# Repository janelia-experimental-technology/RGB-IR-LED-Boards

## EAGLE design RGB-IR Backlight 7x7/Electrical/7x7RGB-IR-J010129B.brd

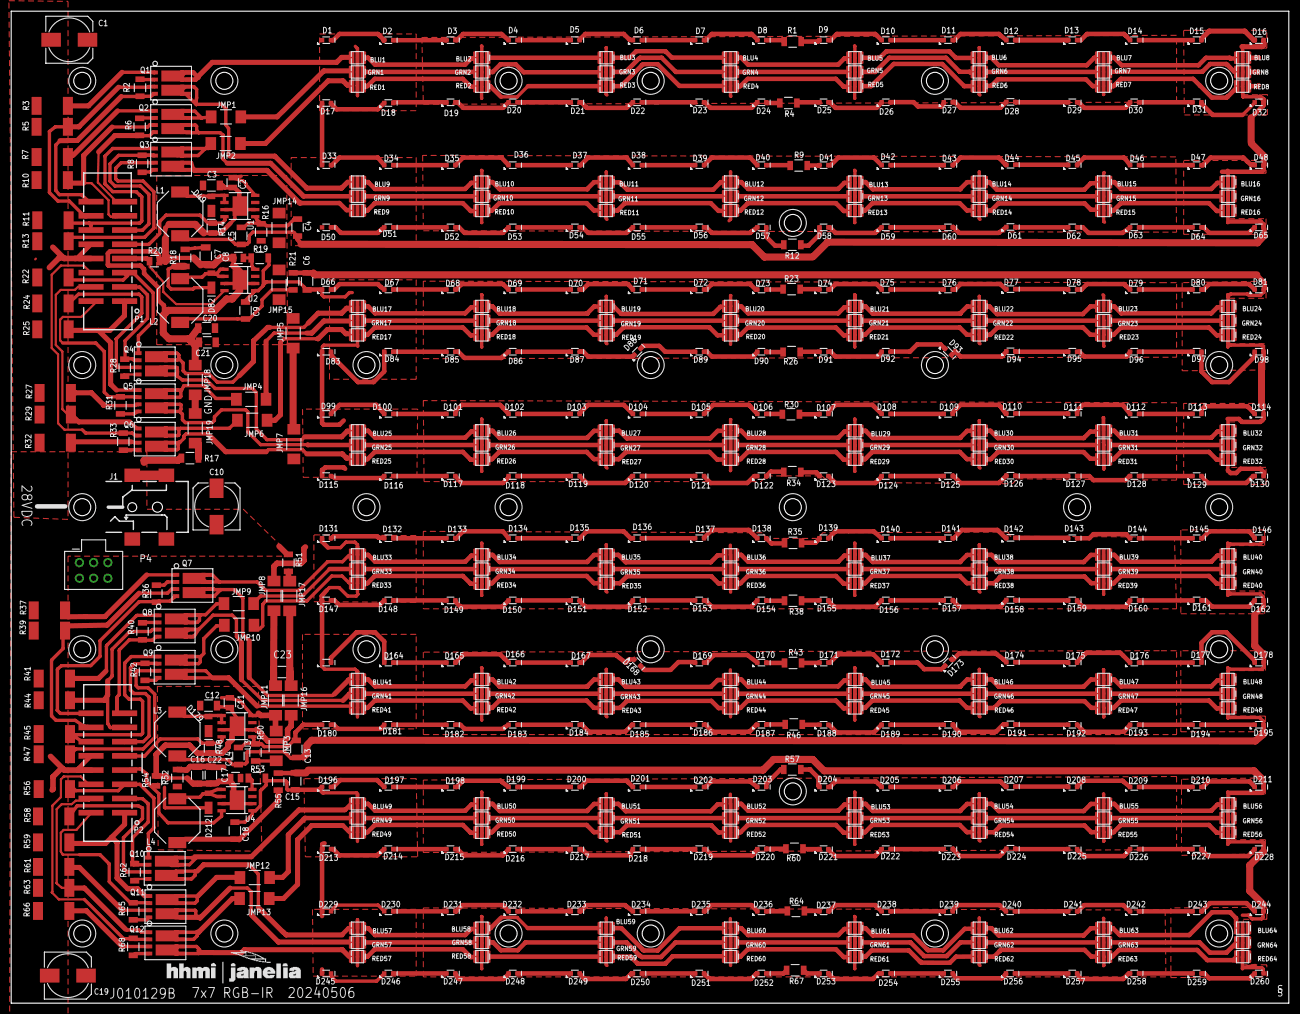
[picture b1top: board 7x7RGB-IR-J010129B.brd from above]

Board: 2 copper layers, 228.3 x 177.3 mm, 617 parts (0 on the bottom side), 537 nets.

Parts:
BLU1, BLU2, BLU3, BLU4, BLU5, BLU6, BLU7, BLU8, BLU9, BLU10, BLU11, BLU12, BLU13, BLU14, BLU15, BLU16, BLU17, BLU18, BLU19, BLU20, BLU21, BLU22, BLU23, BLU24, BLU25, BLU26, BLU27, BLU28, BLU29, BLU30, BLU31, BLU32, BLU33, BLU34, BLU35, BLU36, BLU37, BLU38, BLU39, BLU40, BLU41, BLU42, BLU43, BLU44, BLU45, BLU46, BLU47, BLU48, BLU49, BLU50, BLU51, BLU52, BLU53, BLU54, BLU55, BLU56, BLU57, BLU58, BLU59, BLU60, BLU61, BLU62, BLU63, BLU64: SP-BLU; SUNPLUS-LED
C1, C10, C19: 153CLV-0810
C2, C8, C11, C17: 0.1; 0805S
C3, C7, C12, C16, C20, C21, C22, C23: 10@50; 1210S
C4, C5, C6, C9, C13, C14, C15, C18: 2.2@50; 1206S
D1, D2, D3, D4, D5, D6, D7, D8, D9, D10, D11, D12, D13, D14, D15, D16, D17, D18, D19, D20, D21, D22, D23, D24, D25, D26, D27, D28, D29, D30, D31, D32, D33, D34, D35, D36, D37, D38, D39, D40, D41, D42, D43, D44, D45, D46, D47, D48, D50, D51, D52, D53, D54, D55, D56, D57, D58, D59, D60, D61, D62, D63, D64, D65, D66, D67, D68, D69, D70, D71, D72, D73, D74, D75, D76, D77, D78, D79, D80, D81, D83, D84, D85, D86, D87, D88, D89, D90, D91, D92, D93, D94, D95, D96, D97, D98, D99, D100, D101, D102, D103, D104, D105, D106, D107, D108, D109, D110, D111, D112, D113, D114, D115, D116, D117, D118, D119, D120, D121, D122, D123, D124, D125, D126, D127, D128, D129, D130, D131, D132, D133, D134, D135, D136, D137, D138, D139, D140, D141, D142, D143, D144, D145, D146, D147, D148, D149, D150, D151, D152, D153, D154, D155, D156, D157, D158, D159, D160, D161, D162, D163, D164, D165, D166, D167, D168, D169, D170, D171, D172, D173, D174, D175, D176, D177, D178, D180, D181, D182, D183, D184, D185, D186, D187, D188, D189, D190, D191, D192, D193, D194, D195, D196, D197, D198, D199, D200, D201, D202, D203, D204, D205, D206, D207, D208, D209, D210, D211, D213, D214, D215, D216, D217, D218, D219, D220, D221, D222, D223, D224, D225, D226, D227, D228, D229, D230, D231, D232, D233, D234, D235, D236, D237, D238, D239, D240, D241, D242, D243, D244, D245, D246, D247, D248, D249, D250, D251, D252, D253, D254, D255, D256, D257, D258, D259, D260: LED_SFH4050
D49, D82, D179, D212: DLFS240L; PWRDI-123
GRN1, GRN2, GRN3, GRN4, GRN5, GRN6, GRN7, GRN8, GRN9, GRN10, GRN11, GRN12, GRN13, GRN14, GRN15, GRN16, GRN17, GRN18, GRN19, GRN20, GRN21, GRN22, GRN23, GRN24, GRN25, GRN26, GRN27, GRN28, GRN29, GRN30, GRN31, GRN32, GRN33, GRN34, GRN35, GRN36, GRN37, GRN38, GRN39, GRN40, GRN41, GRN42, GRN43, GRN44, GRN45, GRN46, GRN47, GRN48, GRN49, GRN50, GRN51, GRN52, GRN53, GRN54, GRN55, GRN56, GRN57, GRN58, GRN59, GRN60, GRN61, GRN62, GRN63, GRN64: SP-GRN; SUNPLUS-LED
J1: PJ-002
JMP1, JMP2, JMP3, JMP4, JMP5, JMP6, JMP7, JMP8, JMP9, JMP10, JMP11, JMP12, JMP13, JMP14, JMP15, JMP16, JMP17, JMP18, JMP19: JUMPER5100; 5100
L1, L2, L3, L4: 68uH/1A; SRU8043
P1, P2: HEADER2X8_SM_SMALL
P4: CON2X3; 2X3_PLUG
Q1, Q2, Q3, Q4, Q5, Q6, Q7, Q8, Q9, Q10, Q11, Q12: NPN_DUAL; LFPAK56D
R1, R4, R9, R12, R23, R26, R30, R34, R35, R38, R43, R46, R57, R60, R64, R67: 10R0; 1206S
R2, R8, R36, R42: 10K0; 1206S
R3, R5, R7, R10, R11, R13, R22, R24, R25, R27, R29, R32, R37, R39, R41, R44, R45, R47, R56, R58, R59, R61, R63, R66: 4R99; R2512
R6, R17, R18, R21, R28, R31, R33, R40, R51, R52, R55, R62, R65, R68: 0R0; 1206S
R14, R20, R48, R54: 4.99K; 0805S
R16, R19, R50, R53: 1R00; 1206S
RED1, RED2, RED3, RED4, RED5, RED6, RED7, RED8, RED9, RED10, RED11, RED12, RED13, RED14, RED15, RED16, RED17, RED18, RED19, RED20, RED21, RED22, RED23, RED24, RED25, RED26, RED27, RED28, RED29, RED30, RED31, RED32, RED33, RED34, RED35, RED36, RED37, RED38, RED39, RED40, RED41, RED42, RED43, RED44, RED45, RED46, RED47, RED48, RED49, RED50, RED51, RED52, RED53, RED54, RED55, RED56, RED57, RED58, RED59, RED60, RED61, RED62, RED63, RED64: SP-RED; SUNPLUS-LED
S1, S2, S3, S4, S5, S6, S7, S8, S9, S10, S11, S12, S13, S14, S15, S16, S17, S18, S19, S20, S21, S22, S23, S24, S25, S26, S27, S28, S29, S30, S31, S32: SCREW; 4-40SOCKET
U1, U2, U3, U4: AP8802; SOIC8-EP
U$19: JFRC-LOGOLOGO_OP; LOGO_BMP_OP

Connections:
BLU1: P1.16, Q1.4, R2.1
BLU1F: P1.14, Q1.3, R5.2
BLU1K: BLU1.GC, Q1.7, Q1.8, Q1.78
BLU1K2: BLU9.GC, Q1.5, Q1.6, Q1.56
BLU2: P1.3, Q4.2, R28.2
BLU2F: P1.5, Q4.1, R22.2
BLU2K1: BLU17.GC, Q4.7, Q4.8, Q4.78
BLU2K2: BLU25.GC, Q4.5, Q4.6, Q4.56
BLU3: P2.16, Q7.4, R36.1
BLU3F: P2.14, Q7.3, R39.2
BLU3K: BLU33.GC, Q7.7, Q7.8, Q7.78
BLU4: P2.3, Q10.2, R62.2
BLU4F: P2.5, Q10.1, R56.2
G1: Q5.3, R27.2
G4: Q11.3, R61.2
G4A: Q11.4, R65.1
G4A1: Q5.4, R31.1
GRN1: P1.15, Q2.4, R6.1
GRN1F: P1.13, Q2.3, R10.2
GRN1K: GRN1.GC, JMP1.1
GRN1K2: GRN9.GC, Q2.5, Q2.6, Q2.56
GRN2: P1.2, Q5.2, R31.2
GRN2F: P1.1, Q5.1, R25.2
GRN2K1: GRN17.GC, JMP4.1
GRN2K2: GRN25.GC, Q5.5, Q5.6, Q5.56
GRN3: P2.15, Q8.4, R40.1
GRN3F: P2.13, Q8.3, R44.2
GRN3K: GRN33.GC, JMP9.1
GRN4: P2.2, Q11.2, R65.2
GRN4F: P2.1, Q11.1, R59.2
GULA_1: GRN57.GC, Q11.5, Q11.6, Q11.56
GULA_2: Q12.5, Q12.6, Q12.56, RED57.GC
GULA_3: GRN41.GC, Q8.5, Q8.6, Q8.56
GULA_4: Q9.5, Q9.6, Q9.56, RED41.GC
HS1: BLU2.T, BLU3.T, BLU4.T, BLU5.T, BLU6.T, BLU7.T, GRN2.T, GRN3.T, GRN4.T, GRN5.T, GRN6.T, GRN7.T, RED2.T, RED3.T, RED4.T, RED5.T, RED6.T, RED7.T
HS2: BLU10.T, BLU11.T, BLU12.T, BLU13.T, BLU14.T, BLU15.T, GRN10.T, GRN11.T, GRN12.T, GRN13.T, GRN14.T, GRN15.T, RED10.T, RED11.T, RED12.T, RED13.T, RED14.T, RED15.T
HS3: BLU18.T, BLU19.T, BLU20.T, BLU21.T, BLU22.T, BLU23.T, GRN18.T, GRN19.T, GRN20.T, GRN21.T, GRN22.T, GRN23.T, RED18.T, RED19.T, RED20.T, RED21.T, RED22.T, RED23.T
HS4: BLU26.T, BLU27.T, BLU28.T, BLU29.T, BLU30.T, BLU31.T, GRN26.T, GRN27.T, GRN28.T, GRN29.T, GRN30.T, GRN31.T, RED26.T, RED27.T, RED28.T, RED29.T, RED30.T, RED31.T
HS5: BLU34.T, BLU35.T, BLU36.T, BLU37.T, BLU38.T, BLU39.T, GRN34.T, GRN35.T, GRN36.T, GRN37.T, GRN38.T, GRN39.T, RED34.T, RED35.T, RED36.T, RED37.T, RED38.T, RED39.T
HS6: BLU42.T, BLU43.T, BLU44.T, BLU45.T, BLU46.T, BLU47.T, GRN42.T, GRN43.T, GRN44.T, GRN45.T, GRN46.T, GRN47.T, RED42.T, RED43.T, RED44.T, RED45.T, RED46.T, RED47.T
HS7: BLU50.T, BLU51.T, BLU52.T, BLU53.T, BLU54.T, BLU55.T, GRN50.T, GRN51.T, GRN52.T, GRN53.T, GRN54.T, GRN55.T, RED50.T, RED51.T, RED52.T, RED53.T, RED54.T, RED55.T
HS8: BLU58.T, BLU59.T, BLU60.T, BLU61.T, BLU62.T, BLU63.T, GRN58.T, GRN59.T, GRN60.T, GRN61.T, GRN62.T, GRN63.T, RED58.T, RED59.T, RED60.T, RED61.T, RED62.T, RED63.T
IGND: C11.2, C12.2, C16.2, C17.2, C22.2, C23.2, JMP16.1, JMP16.2, JMP17.1, JMP17.2, R48.1, R51.2, R54.1, U3.2, U3.7, U3.EP, U4.2, U4.7, U4.EP
IGND1: C2.2, C3.2, C7.2, C8.2, C20.2, C21.2, JMP18.1, JMP18.2, JMP19.1, JMP19.2, R14.1, R17.2, R20.1, U1.2, U1.7, U1.EP, U2.2, U2.7, U2.EP
IR_1: P1.9, R14.2, U1.8
IR_2: P1.7, R20.2, U2.8
IR_3: P2.9, R48.2, U3.8
IR_4: P2.7, R54.2, U4.8
IR_DRV3: BLU33.T, BLU41.T, C13.1, C14.1, D131.A, D147.A, D163.A, D180.A, GRN33.T, GRN41.T, R50.1, RED33.T, RED41.T, U3.1
IR_DRV4: BLU49.T, BLU57.T, C15.1, C18.1, D196.A, D213.A, D229.A, D245.A, GRN49.T, GRN57.T, R53.1, RED49.T, RED57.T, U4.1
IR_DRV_UL1: BLU1.T, BLU9.T, C4.1, C5.1, D1.A, D17.A, D33.A, D50.A, GRN1.T, GRN9.T, R16.1, RED1.T, RED9.T, U1.1
IR_DRV_UL2: BLU17.T, BLU25.T, C6.1, C9.1, D66.A, D83.A, D99.A, D115.A, GRN17.T, GRN25.T, R19.1, RED17.T, RED25.T, U2.1
IR_RET2: BLU24.T, BLU32.T, C6.2, D81.C, D98.C, D114.C, D130.C, GRN24.T, GRN32.T, R21.2, RED24.T, RED32.T
IR_RET3: BLU40.T, BLU48.T, C13.2, C14.2, D146.C, D162.C, D178.C, D195.C, GRN40.T, GRN48.T, L3.1, RED40.T, RED48.T
IR_RET_UL1: BLU8.T, BLU16.T, C4.2, C5.2, D16.C, D32.C, D48.C, D65.C, GRN8.T, GRN16.T, L1.1, RED8.T, RED16.T
I_RET4: BLU56.T, BLU64.T, C15.2, D211.C, D228.C, D244.C, D260.C, GRN56.T, GRN64.T, R55.2, RED56.T, RED64.T
LGND: C1.-, C10.-, C19.-, J1.2, P1.8, P1.10, P2.8, P2.10, P4.1, P4.3, R3.1, R5.1, R7.1, R10.1, R11.1, R13.1, R17.1, R22.1, R24.1, R25.1, R27.1, R29.1, R32.1, R37.1, R39.1, R41.1, R44.1, R45.1, R47.1, R51.1, R56.1, R58.1, R59.1, R61.1, R63.1, R66.1
unnamed: GRN10.GA, GRN11.GC
unnamed: D227.C, D228.A
unnamed: Q12.4, R68.1
unnamed: Q8.1, R41.2
unnamed: GRN49.GC, JMP12.1
unnamed: BLU49.GC, Q10.7, Q10.8, Q10.78
unnamed: GRN9.GA, GRN10.GC
unnamed: BLU57.GC, Q10.5, Q10.6, Q10.56
unnamed: Q9.3, R47.2
unnamed: Q9.4, R42.1
unnamed: Q8.2, R40.2
unnamed: RED10.GA, RED11.GC
unnamed: RED9.GA, RED10.GC
unnamed: D139.A, R35.1
unnamed: JMP13.2, Q12.7, Q12.8, Q12.78
unnamed: JMP12.2, Q11.7, Q11.8, Q11.78
unnamed: D138.C, R35.2
unnamed: D154.C, R38.2
unnamed: D155.A, R38.1
unnamed: JMP13.1, RED49.GC
unnamed: D171.A, R43.1
unnamed: D170.C, R43.2
unnamed: D188.A, R46.1
unnamed: D187.C, R46.2
unnamed: D203.C, R57.2
unnamed: GRN58.GA, GRN59.GC
unnamed: D212.A, L4.2, U4.5, U4.6
unnamed: GRN5.GA, GRN6.GC
unnamed: C18.2, L4.1, R55.1
unnamed: GRN57.GA, GRN58.GC
unnamed: D204.A, R57.1
unnamed: D221.A, R60.1
unnamed: D220.C, R60.2
unnamed: D237.A, R64.1
unnamed: Q10.4, R62.1
unnamed: Q10.3, R58.2
unnamed: D236.C, R64.2
unnamed: D253.A, R67.1
unnamed: D252.C, R67.2
unnamed: BLU9.GA, BLU10.GC
unnamed: BLU10.GA, BLU11.GC
unnamed: GRN13.GA, GRN14.GC
unnamed: GRN12.GA, GRN13.GC
unnamed: RED13.GA, RED14.GC
unnamed: RED12.GA, RED13.GC
unnamed: BLU12.GA, BLU13.GC
unnamed: BLU13.GA, BLU14.GC
unnamed: GRN15.GA, GRN16.GC
unnamed: RED15.GA, RED16.GC
unnamed: BLU15.GA, BLU16.GC
unnamed: BLU11.GA, BLU12.GC
unnamed: RED11.GA, RED12.GC
unnamed: GRN11.GA, GRN12.GC
unnamed: GRN18.GA, GRN19.GC
unnamed: BLU14.GA, BLU15.GC
unnamed: RED14.GA, RED15.GC
unnamed: D51.C, D52.A
unnamed: D52.C, D53.A
unnamed: D54.C, D55.A
unnamed: D56.C, D57.A
unnamed: D50.C, D51.A
unnamed: D53.C, D54.A
unnamed: D55.C, D56.A
unnamed: D59.C, D60.A
unnamed: D60.C, D61.A
unnamed: D62.C, D63.A
unnamed: D179.A, L3.2, U3.5, U3.6
unnamed: D64.C, D65.A
unnamed: D58.C, D59.A
unnamed: D61.C, D62.A
unnamed: D63.C, D64.A
unnamed: D34.C, D35.A
unnamed: D35.C, D36.A
unnamed: D37.C, D38.A
unnamed: D39.C, D40.A
unnamed: D33.C, D34.A
unnamed: D36.C, D37.A
unnamed: D38.C, D39.A
unnamed: D42.C, D43.A
unnamed: D43.C, D44.A
unnamed: D45.C, D46.A
unnamed: D47.C, D48.A
unnamed: D41.C, D42.A
unnamed: D44.C, D45.A
unnamed: D46.C, D47.A
unnamed: GRN17.GA, GRN18.GC
unnamed: RED18.GA, RED19.GC
unnamed: RED17.GA, RED18.GC
unnamed: BLU17.GA, BLU18.GC
unnamed: BLU18.GA, BLU19.GC
unnamed: GRN21.GA, GRN22.GC
unnamed: GRN20.GA, GRN21.GC
unnamed: RED21.GA, RED22.GC
unnamed: RED20.GA, RED21.GC
unnamed: BLU20.GA, BLU21.GC
unnamed: BLU21.GA, BLU22.GC
unnamed: GRN42.GA, GRN43.GC
unnamed: GRN23.GA, GRN24.GC
unnamed: RED23.GA, RED24.GC
unnamed: BLU23.GA, BLU24.GC
unnamed: BLU19.GA, BLU20.GC
unnamed: RED19.GA, RED20.GC
unnamed: GRN19.GA, GRN20.GC
unnamed: GRN26.GA, GRN27.GC
unnamed: BLU22.GA, BLU23.GC
unnamed: RED22.GA, RED23.GC
unnamed: GRN22.GA, GRN23.GC
unnamed: D67.C, D68.A
unnamed: D68.C, D69.A
unnamed: D70.C, D71.A
unnamed: D72.C, D73.A
unnamed: D66.C, D67.A
unnamed: D69.C, D70.A
unnamed: D71.C, D72.A
unnamed: D75.C, D76.A
unnamed: D76.C, D77.A
unnamed: D78.C, D79.A
unnamed: D80.C, D81.A
unnamed: D74.C, D75.A
unnamed: D77.C, D78.A
unnamed: D79.C, D80.A
unnamed: D84.C, D85.A
unnamed: D85.C, D86.A
unnamed: D87.C, D88.A
unnamed: D89.C, D90.A
unnamed: D83.C, D84.A
unnamed: D86.C, D87.A
unnamed: D88.C, D89.A
unnamed: D92.C, D93.A
unnamed: D94.C, D95.A
unnamed: D96.C, D97.A
unnamed: D91.C, D92.A
unnamed: D93.C, D94.A
unnamed: D95.C, D96.A
unnamed: GRN4.GA, GRN5.GC
unnamed: RED5.GA, RED6.GC
unnamed: RED4.GA, RED5.GC
unnamed: BLU4.GA, BLU5.GC
unnamed: BLU5.GA, BLU6.GC
unnamed: GRN2.GA, GRN3.GC
unnamed: GRN1.GA, GRN2.GC
unnamed: GRN7.GA, GRN8.GC
unnamed: RED7.GA, RED8.GC
unnamed: BLU7.GA, BLU8.GC
unnamed: BLU3.GA, BLU4.GC
unnamed: RED3.GA, RED4.GC
unnamed: RED2.GA, RED3.GC
unnamed: RED1.GA, RED2.GC
unnamed: BLU1.GA, BLU2.GC
unnamed: BLU2.GA, BLU3.GC
unnamed: GRN3.GA, GRN4.GC
unnamed: GRN14.GA, GRN15.GC
unnamed: BLU6.GA, BLU7.GC
unnamed: RED6.GA, RED7.GC
unnamed: GRN6.GA, GRN7.GC
unnamed: D2.C, D3.A
unnamed: D3.C, D4.A
unnamed: D5.C, D6.A
unnamed: D7.C, D8.A
unnamed: D1.C, D2.A
unnamed: D4.C, D5.A
unnamed: D6.C, D7.A
unnamed: D10.C, D11.A
unnamed: D11.C, D12.A
unnamed: D13.C, D14.A
unnamed: D15.C, D16.A
unnamed: D9.C, D10.A
unnamed: D12.C, D13.A
unnamed: D14.C, D15.A
unnamed: D18.C, D19.A
unnamed: D19.C, D20.A
unnamed: D21.C, D22.A
unnamed: D23.C, D24.A
unnamed: D17.C, D18.A
unnamed: D20.C, D21.A
unnamed: D22.C, D23.A
unnamed: GRN41.GA, GRN42.GC
unnamed: RED42.GA, RED43.GC
unnamed: RED41.GA, RED42.GC
unnamed: D26.C, D27.A
unnamed: BLU41.GA, BLU42.GC
unnamed: D27.C, D28.A
unnamed: D29.C, D30.A
unnamed: D31.C, D32.A
unnamed: D25.C, D26.A
unnamed: D28.C, D29.A
unnamed: D30.C, D31.A
unnamed: BLU42.GA, BLU43.GC
unnamed: Q1.1, R3.2
unnamed: RED58.GA, RED59.GC
unnamed: GRN25.GA, GRN26.GC
unnamed: RED26.GA, RED27.GC
unnamed: RED25.GA, RED26.GC
unnamed: BLU25.GA, BLU26.GC
unnamed: BLU26.GA, BLU27.GC
unnamed: GRN29.GA, GRN30.GC
unnamed: GRN28.GA, GRN29.GC
unnamed: RED29.GA, RED30.GC
unnamed: RED28.GA, RED29.GC
unnamed: BLU28.GA, BLU29.GC
unnamed: BLU29.GA, BLU30.GC
unnamed: GRN31.GA, GRN32.GC
unnamed: RED31.GA, RED32.GC
unnamed: BLU31.GA, BLU32.GC
unnamed: BLU27.GA, BLU28.GC
unnamed: RED27.GA, RED28.GC
unnamed: GRN27.GA, GRN28.GC
unnamed: GRN34.GA, GRN35.GC
unnamed: BLU30.GA, BLU31.GC
unnamed: RED30.GA, RED31.GC
unnamed: GRN30.GA, GRN31.GC
unnamed: D100.C, D101.A
unnamed: D101.C, D102.A
unnamed: D103.C, D104.A
unnamed: D105.C, D106.A
unnamed: D99.C, D100.A
unnamed: D102.C, D103.A
unnamed: D104.C, D105.A
unnamed: D108.C, D109.A
unnamed: D109.C, D110.A
unnamed: D111.C, D112.A
unnamed: D113.C, D114.A
unnamed: D107.C, D108.A
unnamed: D110.C, D111.A
unnamed: D112.C, D113.A
unnamed: D116.C, D117.A
unnamed: D117.C, D118.A
unnamed: D119.C, D120.A
unnamed: D121.C, D122.A
unnamed: GRN45.GA, GRN46.GC
unnamed: D115.C, D116.A
unnamed: D118.C, D119.A
unnamed: GRN44.GA, GRN45.GC
unnamed: D120.C, D121.A
unnamed: RED45.GA, RED46.GC
unnamed: D124.C, D125.A
unnamed: D125.C, D126.A
unnamed: RED44.GA, RED45.GC
unnamed: BLU44.GA, BLU45.GC
unnamed: BLU45.GA, BLU46.GC
unnamed: GRN47.GA, GRN48.GC
unnamed: RED47.GA, RED48.GC
unnamed: BLU47.GA, BLU48.GC
unnamed: BLU43.GA, BLU44.GC
unnamed: RED43.GA, RED44.GC
unnamed: D127.C, D128.A
unnamed: D129.C, D130.A
unnamed: GRN43.GA, GRN44.GC
unnamed: GRN50.GA, GRN51.GC
unnamed: BLU46.GA, BLU47.GC
unnamed: RED46.GA, RED47.GC
unnamed: D123.C, D124.A
unnamed: D126.C, D127.A
unnamed: D128.C, D129.A
unnamed: JMP2.2, Q3.7, Q3.8, Q3.78
unnamed: D181.C, D182.A
unnamed: D182.C, D183.A
unnamed: JMP1.2, Q2.7, Q2.8, Q2.78
unnamed: Q1.2, R2.2
unnamed: D97.C, D98.A
unnamed: GRN33.GA, GRN34.GC
unnamed: RED34.GA, RED35.GC
unnamed: JMP6.2, Q6.7, Q6.8, Q6.78
unnamed: D184.C, D185.A
unnamed: D186.C, D187.A
unnamed: JMP4.2, Q5.7, Q5.8, Q5.78
unnamed: RED33.GA, RED34.GC
unnamed: D180.C, D181.A
unnamed: D183.C, D184.A
unnamed: D185.C, D186.A
unnamed: D189.C, D190.A
unnamed: D190.C, D191.A
unnamed: D192.C, D193.A
unnamed: D194.C, D195.A
unnamed: D188.C, D189.A
unnamed: D191.C, D192.A
unnamed: D193.C, D194.A
unnamed: D164.C, D165.A
unnamed: D165.C, D166.A
unnamed: D167.C, D168.A
unnamed: D169.C, D170.A
unnamed: D163.C, D164.A
unnamed: D166.C, D167.A
unnamed: D168.C, D169.A
unnamed: D172.C, D173.A
unnamed: D173.C, D174.A
unnamed: D175.C, D176.A
unnamed: D177.C, D178.A
unnamed: D171.C, D172.A
unnamed: D174.C, D175.A
unnamed: D176.C, D177.A
unnamed: BLU33.GA, BLU34.GC
unnamed: D49.A, L1.2, U1.5, U1.6
unnamed: GRN49.GA, GRN50.GC
unnamed: RED50.GA, RED51.GC
unnamed: RED49.GA, RED50.GC
unnamed: BLU49.GA, BLU50.GC
unnamed: BLU50.GA, BLU51.GC
unnamed: GRN53.GA, GRN54.GC
unnamed: GRN52.GA, GRN53.GC
unnamed: RED53.GA, RED54.GC
unnamed: RED52.GA, RED53.GC
unnamed: BLU52.GA, BLU53.GC
unnamed: BLU53.GA, BLU54.GC
unnamed: GRN55.GA, GRN56.GC
unnamed: RED55.GA, RED56.GC
unnamed: BLU55.GA, BLU56.GC
unnamed: BLU51.GA, BLU52.GC
unnamed: RED51.GA, RED52.GC
unnamed: GRN51.GA, GRN52.GC
unnamed: RED57.GA, RED58.GC
unnamed: BLU54.GA, BLU55.GC
unnamed: RED54.GA, RED55.GC
unnamed: GRN54.GA, GRN55.GC
unnamed: D197.C, D198.A
unnamed: D198.C, D199.A
unnamed: D200.C, D201.A
unnamed: D202.C, D203.A
unnamed: D196.C, D197.A
unnamed: D199.C, D200.A
unnamed: D201.C, D202.A
unnamed: D205.C, D206.A
unnamed: D206.C, D207.A
unnamed: D208.C, D209.A
unnamed: D210.C, D211.A
unnamed: D204.C, D205.A
unnamed: D207.C, D208.A
unnamed: D209.C, D210.A
unnamed: D214.C, D215.A
unnamed: D215.C, D216.A
unnamed: D217.C, D218.A
unnamed: D219.C, D220.A
unnamed: D213.C, D214.A
unnamed: D216.C, D217.A
unnamed: D218.C, D219.A
unnamed: D222.C, D223.A
unnamed: D224.C, D225.A
unnamed: D226.C, D227.A
unnamed: D221.C, D222.A
unnamed: D223.C, D224.A
unnamed: D225.C, D226.A
unnamed: D82.A, L2.2, U2.5, U2.6
unnamed: BLU34.GA, BLU35.GC
unnamed: GRN37.GA, GRN38.GC
unnamed: GRN36.GA, GRN37.GC
unnamed: RED37.GA, RED38.GC
unnamed: RED36.GA, RED37.GC
unnamed: BLU36.GA, BLU37.GC
unnamed: BLU37.GA, BLU38.GC
unnamed: GRN39.GA, GRN40.GC
unnamed: RED39.GA, RED40.GC
unnamed: BLU39.GA, BLU40.GC
unnamed: BLU35.GA, BLU36.GC
unnamed: RED35.GA, RED36.GC
unnamed: GRN35.GA, GRN36.GC
unnamed: GRN46.GA, GRN47.GC
unnamed: BLU38.GA, BLU39.GC
unnamed: RED38.GA, RED39.GC
unnamed: GRN38.GA, GRN39.GC
unnamed: BLU57.GA, BLU58.GC
unnamed: BLU58.GA, BLU59.GC
unnamed: GRN61.GA, GRN62.GC
unnamed: GRN60.GA, GRN61.GC
unnamed: D132.C, D133.A
unnamed: D133.C, D134.A
unnamed: D135.C, D136.A
unnamed: D137.C, D138.A
unnamed: D131.C, D132.A
unnamed: D134.C, D135.A
unnamed: D136.C, D137.A
unnamed: D140.C, D141.A
unnamed: D141.C, D142.A
unnamed: D143.C, D144.A
unnamed: D145.C, D146.A
unnamed: D139.C, D140.A
unnamed: D142.C, D143.A
unnamed: D144.C, D145.A
unnamed: D148.C, D149.A
unnamed: D149.C, D150.A
unnamed: D151.C, D152.A
unnamed: D153.C, D154.A
unnamed: D147.C, D148.A
unnamed: D150.C, D151.A
unnamed: D152.C, D153.A
unnamed: D156.C, D157.A
unnamed: D157.C, D158.A
unnamed: D159.C, D160.A
unnamed: D161.C, D162.A
unnamed: D155.C, D156.A
unnamed: D158.C, D159.A
unnamed: D160.C, D161.A
unnamed: C9.2, L2.1, R21.1
unnamed: JMP5.1, JMP7.2
unnamed: Q6.4, R33.1
unnamed: Q4.4, R28.1
unnamed: Q4.3, R24.2
unnamed: Q3.3, R13.2
unnamed: Q3.4, R8.1
unnamed: Q7.1, R37.2
unnamed: BLU41.GC, Q7.5, Q7.6, Q7.56
unnamed: Q2.1, R7.2
unnamed: RED61.GA, RED62.GC
unnamed: RED60.GA, RED61.GC
unnamed: BLU60.GA, BLU61.GC
unnamed: BLU61.GA, BLU62.GC
unnamed: GRN63.GA, GRN64.GC
unnamed: RED63.GA, RED64.GC
unnamed: BLU63.GA, BLU64.GC
unnamed: BLU59.GA, BLU60.GC
unnamed: RED59.GA, RED60.GC
unnamed: GRN59.GA, GRN60.GC
unnamed: BLU62.GA, BLU63.GC
unnamed: RED62.GA, RED63.GC
unnamed: GRN62.GA, GRN63.GC
unnamed: D230.C, D231.A
unnamed: D231.C, D232.A
unnamed: D233.C, D234.A
unnamed: D235.C, D236.A
unnamed: D229.C, D230.A
unnamed: D232.C, D233.A
unnamed: D234.C, D235.A
unnamed: D238.C, D239.A
unnamed: D239.C, D240.A
unnamed: D241.C, D242.A
unnamed: D243.C, D244.A
unnamed: D237.C, D238.A
unnamed: D240.C, D241.A
unnamed: D242.C, D243.A
unnamed: D246.C, D247.A
unnamed: D247.C, D248.A
unnamed: D249.C, D250.A
unnamed: D251.C, D252.A
unnamed: D245.C, D246.A
unnamed: D248.C, D249.A
unnamed: D250.C, D251.A
unnamed: D254.C, D255.A
unnamed: D255.C, D256.A
unnamed: D257.C, D258.A
unnamed: D259.C, D260.A
unnamed: D253.C, D254.A
unnamed: D256.C, D257.A
unnamed: D258.C, D259.A
unnamed: Q2.2, R6.2
unnamed: D9.A, R1.1
unnamed: D8.C, R1.2
unnamed: D24.C, R4.2
unnamed: D25.A, R4.1
unnamed: D41.A, R9.1
unnamed: D40.C, R9.2
unnamed: D58.A, R12.1
unnamed: D57.C, R12.2
unnamed: D73.C, R23.2
unnamed: D74.A, R23.1
unnamed: D91.A, R26.1
unnamed: D90.C, R26.2
unnamed: D107.A, R30.1
unnamed: D106.C, R30.2
unnamed: D123.A, R34.1
unnamed: D122.C, R34.2
unnamed: JMP10.2, Q9.7, Q9.8, Q9.78
unnamed: JMP9.2, Q8.7, Q8.8, Q8.78
unnamed: Q7.2, R36.2
R1: Q6.3, R32.2
R4: Q12.3, R66.2
RED1: P1.11, Q3.2, R8.2
RED1F: P1.12, Q3.1, R11.2
RED1K: JMP2.1, RED1.GC
RED1K2: Q3.5, Q3.6, Q3.56, RED9.GC
RED2: P1.6, Q6.2, R33.2
RED2F: P1.4, Q6.1, R29.2
RED2K1: JMP6.1, RED17.GC
RED2K2: Q6.5, Q6.6, Q6.56, RED25.GC
RED3: P2.11, Q9.2, R42.2
RED3F: P2.12, Q9.1, R45.2
RED3K: JMP10.1, RED33.GC
RED4: P2.6, Q12.2, R68.2
RED4F: P2.4, Q12.1, R63.2
VIR1: C2.1, C3.1, C7.1, C8.1, C20.1, C21.1, D49.K, D82.K, JMP5.2, JMP14.1, JMP14.2, JMP15.1, JMP15.2, R16.2, R18.1, R18.2, R19.2, U1.4, U2.4
V_IR: C11.1, C12.1, C16.1, C17.1, C22.1, C23.1, D179.K, D212.K, JMP3.1, JMP3.2, JMP8.2, JMP11.1, JMP11.2, R50.2, R52.1, R52.2, R53.2, U3.4, U4.4
V_RGB: BLU8.GA, BLU16.GA, BLU24.GA, BLU32.GA, BLU40.GA, BLU48.GA, BLU56.GA, BLU64.GA, C1.+, C10.+, C19.+, GRN8.GA, GRN16.GA, GRN24.GA, GRN32.GA, GRN40.GA, GRN48.GA, GRN56.GA, GRN64.GA, J1.1A, J1.1B, JMP7.1, JMP8.1, P4.2, P4.4, RED8.GA, RED16.GA, RED24.GA, RED32.GA, RED40.GA, RED48.GA, RED56.GA, RED64.GA
